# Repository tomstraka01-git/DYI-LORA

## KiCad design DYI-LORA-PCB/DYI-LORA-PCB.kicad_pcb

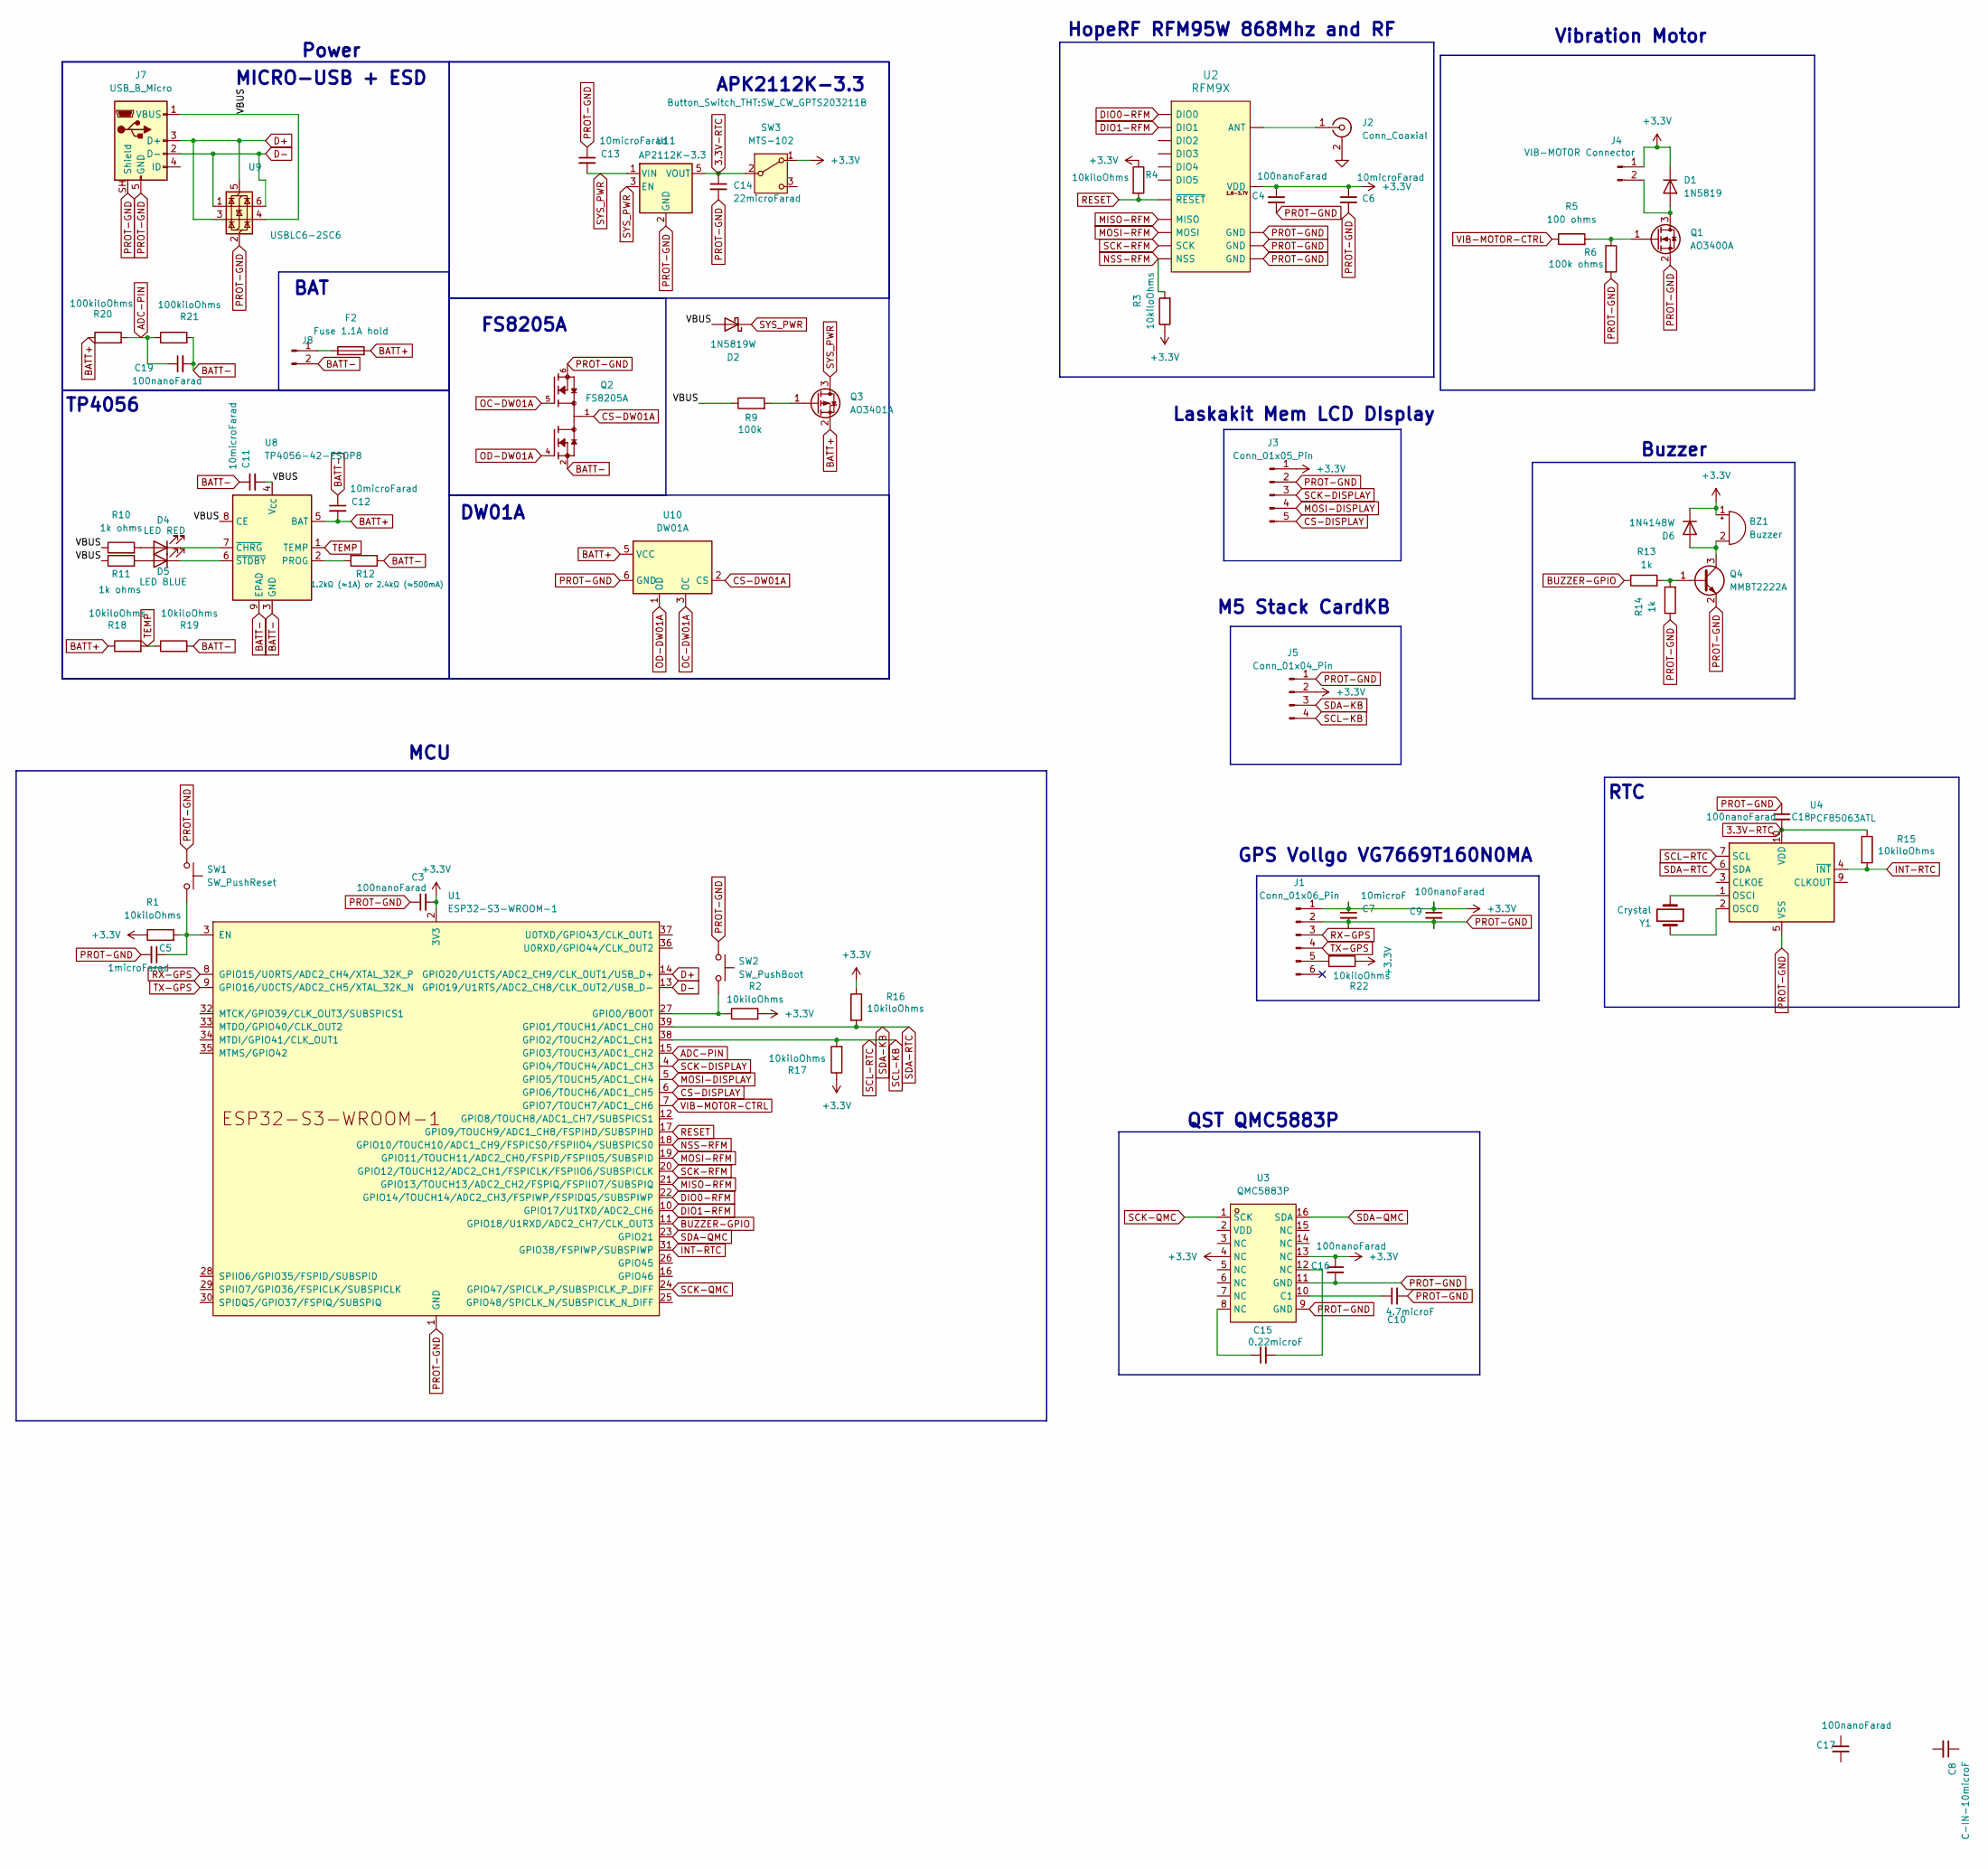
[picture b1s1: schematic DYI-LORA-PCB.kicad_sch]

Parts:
BZ1: Buzzer; MagneticBuzzer_PUI_AT-0927-TT-6-R
C3, C4, C9, C16, C17, C18, C19: 100nanoFarad; C_0603_1608Metric_Pad1.08x0.95mm_HandSolder
C5: 1microFarad; C_1206_3216Metric_Pad1.33x1.80mm_HandSolder
C6, C11, C12, C13: 10microFarad; C_0805_2012Metric_Pad1.18x1.45mm_HandSolder
C7: 10microF; C_0805_2012Metric_Pad1.18x1.45mm_HandSolder
C8: C-IN-10microF; C_0805_2012Metric_Pad1.18x1.45mm_HandSolder
C10: 4.7microF; C_0805_2012Metric_Pad1.18x1.45mm_HandSolder
C14: 22microFarad; C_1206_3216Metric_Pad1.33x1.80mm_HandSolder
C15: 0.22microF; C_0805_2012Metri
D1: 1N5819; D_SOD-123
D2: 1N5819W; D_SOD-123
D4: LED RED; LED_0805_2012Metric_Pad1.15x1.40mm_HandSolder
D5: LED BLUE; LED_0805_2012Metric_Pad1.15x1.40mm_HandSolder
D6: 1N4148W; D_SOD-123
F2: Fuse 1.1A hold; Fuse_1206_3216Metric_Pad1.42x1.75mm_HandSolder
J1: Conn_01x06_Pin; JST_SH_SM06B-SRSS-TB_1x06-1MP_P1.00mm_Horizontal
J2: Conn_Coaxial; SMA_Amphenol_132134-11_Vertical
J3: Conn_01x05_Pin; PinHeader_1x05_P2.54mm_Vertical
J4: VIB-MOTOR Connector; PinHeader_1x02_P2.54mm_Vertical
J5: Conn_01x04_Pin; JST_SH_SM04B-SRSS-TB_1x04-1MP_P1.00mm_Horizontal
J7: USB_B_Micro; USB_Micro-B_Molex_47346-0001
J8: Conn_01x02_Pin; JST_PH_S2B-PH-K_1x02_P2.00mm_Horizontal
Q1: AO3400A; SOT-23_Handsoldering
Q2: FS8205A; TSSOP-8_4.4x3mm_P0.65mm; PARTREV 1.7
Q3: AO3401A; SOT-23_Handsoldering
Q4: MMBT2222A; SOT-23_Handsoldering
R1, R2, R3, R4, R15, R16, R17, R18, R19, R22: 10kiloOhms; R_1206_3216Metric_Pad1.30x1.75mm_HandSolder
R5: 100 ohms; R_1206_3216Metric_Pad1.30x1.75mm_HandSolder
R6: 100k ohms; R_1206_3216Metric_Pad1.30x1.75mm_HandSolder
R9: 100k; R_0805_2012Metric_Pad1.20x1.40mm_HandSolder
R10, R11: 1k ohms; R_1206_3216Metric_Pad1.30x1.75mm_HandSolder
R12: 1.2kΩ (≈1A) or 2.4kΩ (≈500mA); R_1206_3216Metric_Pad1.30x1.75mm_HandSolder
R13, R14: 1k; R_0805_2012Metric_Pad1.20x1.40mm_HandSolder
R20, R21: 100kiloOhms; R_1206_3216Metric_Pad1.30x1.75mm_HandSolder
SW1: SW_PushReset; SW_PUSH_6mm_H4.3mm
SW2: SW_PushBoot; SW_PUSH_6mm_H4.3mm
SW3: MTS-102; SW_CW_GPTS203211B
U1: ESP32-S3-WROOM-1
U2: RFM9X; RFM9X-SMD
U3: QMC5883P; LGA-16_3x3mm_P0.5mm; MPN QMC5883P; LCSC Part C2847467
U4: PCF85063ATL; DFN-10-1EP_2.6x2.6mm_P0.5mm_EP1.3x2.2mm
U8: TP4056-42-ESOP8; SOIC-8-1EP_3.9x4.9mm_P1.27mm_EP2.41x3.3mm_ThermalVias
U9: USBLC6-2SC6; SOT-23-6
U10: DW01A; SOT-23-6
U11: AP2112K-3.3; SOT-23-5_HandSoldering
Y1: Crystal; Crystal_SMD_3215-2Pin_3.2x1.5mm

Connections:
3.3V-RTC: C14.1, C18.2, R15.1, SW3.2 (B), U4.10 (VDD), U11.5 (VOUT)
+3.3V: BZ1.1 (+), C3.2, C4.1, C6.1, C7.1, C9.1, C16.1, D1.1 (K), D6.1 (K), J1.1, J3.1, J4.1, J5.2, R1.1, R2.2, R3.1, R4.1, R16.1, R17.1, R22.1, SW3.1 (A), U1.2 (3V3), U2.13 (VDD), U3.4 (NC), U3.13 (NC)
/VBUS: C11.2, D2.2 (A), J7.1 (VBUS), R9.1, R10.1, R11.1, U8.4 (V_{CC}), U8.8 (CE), U9.4 (I/O2)
ADC-PIN: C19.1, R20.2, R21.1, U1.15 (GPIO3/TOUCH3/ADC1_CH2)
BATT+: C12.2, F2.2, Q3.2 (S), R18.1, R20.1, U8.5 (BAT), U10.5 (VCC)
BATT-: C11.1, C12.1, C19.2, J8.2, Q2.2, Q2.3, R12.1, R19.2, R21.2, U8.3 (GND), U8.9 (EPAD)
BUZZER-GPIO: R13.1, U1.11 (GPIO18/U1RXD/ADC2_CH7/CLK_OUT3)
CS-DISPLAY: J3.5, U1.6 (GPIO6/TOUCH6/ADC1_CH5)
CS-DW01A: Q2.1, Q2.8, U10.2 (CS)
D+: J7.3 (D+), U1.14 (GPIO20/U1CTS/ADC2_CH9/CLK_OUT1/USB_D+), U9.3 (I/O2), U9.5 (VBUS)
D-: J7.2 (D-), U1.13 (GPIO19/U1RTS/ADC2_CH8/CLK_OUT2/USB_D-), U9.1 (I/O1), U9.6 (I/O1)
DIO0-RFM: U1.22 (GPIO14/TOUCH14/ADC2_CH3/FSPIWP/FSPIDQS/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), U2.14 (DIO0)
DIO1-RFM: U1.10 (GPIO17/U1TXD/ADC2_CH6), U2.15 (DIO1)
GND: J2.2 (Ext)
INT-RTC: R15.2, U1.31 (GPIO38/FSPIWP/SUBSPIWP), U4.4 (~INT)
MISO-RFM: U1.21 (GPIO13/TOUCH13/ADC2_CH2/FSPIQ/FSPIIO7/S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), U2.2 (MISO)
MOSI-DISPLAY: J3.4, U1.5 (GPIO5/TOUCH5/ADC1_CH4)
MOSI-RFM: U1.19 (GPIO11/TOUCH11/ADC2_CH0/FSPID/FSPIIO5/S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), U2.3 (MOSI)
NSS-RFM: R3.2, U1.18 (GPIO10/TOUCH10/ADC1_CH9/FSPICS0/FSPIIO4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), U2.5 (NSS)
unnamed: BZ1.2 (-), D6.2 (A), Q4.3 (C)
unnamed: C15.1, U3.8 (NC)
unnamed: C15.2, U3.12 (NC)
unnamed: D1.2 (A), J4.2, Q1.3 (D)
unnamed: D4.2 (A), R10.2
unnamed: D4.1 (K), U8.7 (~CHRG)
unnamed: D5.2 (A), R11.2
unnamed: D5.1 (K), U8.6 (~STDBY)
unnamed: J1.5, R22.2
unnamed: J2.1 (In), U2.9 (ANT)
unnamed: F2.1, J8.1
unnamed: Q1.1 (G), R5.2, R6.1
unnamed: Q3.1 (G), R9.2
unnamed: Q4.1 (B), R13.2, R14.2
unnamed: C5.1, R1.2, SW1.2, U1.3 (EN)
unnamed: R2.1, SW2.2, U1.27 (GPIO0/BOOT)
unnamed: C10.1, U3.10 (C1)
unnamed: U4.1 (OSCI), Y1.1
unnamed: U4.2 (OSCO), Y1.2
unnamed: R12.2, U8.2 (PROG)
OC-DW01A: Q2.5, U10.3 (OC)
OD-DW01A: Q2.4, U10.1 (OD)
PROT-GND: C3.1, C4.2, C5.2, C6.2, C7.2, C9.2, C10.2, C13.1, C14.2, C16.2, C18.1, J1.2, J3.2, J5.1, J7.5 (GND), J7.SH (Shield), Q1.2 (S), Q2.6, Q2.7, Q4.2 (E), R6.2, R14.1, SW1.1, SW2.1, U1.1 (GND), U1.40 (GND), U1.41 (GND), U2.1 (GND), U2.8 (GND), U2.10 (GND), U3.9 (GND), U3.11 (GND), U4.5 (VSS), U9.2 (GND), U10.6 (GND), U11.2 (GND)
RESET: R4.2, U1.17 (GPIO9/TOUCH9/ADC1_CH8/FSPIHD/SUBSPIHD), U2.6 (~RESET)
RX-GPS: J1.3, U1.8 (GPIO15/U0RTS/ADC2_CH4/XTAL_32K_P)
SCK-DISPLAY: J3.3, U1.4 (GPIO4/TOUCH4/ADC1_CH3)
SCK-QMC: U1.24 (GPIO47/SPICLK_P/SUBSPICLK_P_DIFF), U3.1 (SCK)
SCK-RFM: U1.20 (GPIO12/TOUCH12/ADC2_CH1/FSPICLK/FSPIIO6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), U2.4 (SCK)
SCL-KB: J5.4, R17.2, U1.38 (GPIO2/TOUCH2/ADC1_CH1), U4.7 (SCL)
SDA-KB: J5.3, R16.2, U1.39 (GPIO1/TOUCH1/ADC1_CH0), U4.6 (SDA)
SDA-QMC: U1.23 (GPIO21), U3.16 (SDA)
SYS_PWR: C13.2, D2.1 (K), Q3.3 (D), U11.1 (VIN), U11.3 (EN)
TEMP: R18.2, R19.1, U8.1 (TEMP)
TX-GPS: J1.4, U1.9 (GPIO16/U0CTS/ADC2_CH5/XTAL_32K_N)
VIB-MOTOR-CTRL: R5.1, U1.7 (GPIO7/TOUCH7/ADC1_CH6)

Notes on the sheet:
RTC
TP4056
Vibration Motor
MCU
Buzzer
Power
GPS Vollgo VG7669T160N0MA
MICRO-USB + ESD
Laskakit Mem LCD DIsplay
APK2112K-3.3
HopeRF RFM95W 868Mhz and RF
QST QMC5883P
DW01A
M5 Stack CardKB
FS8205A
BAT

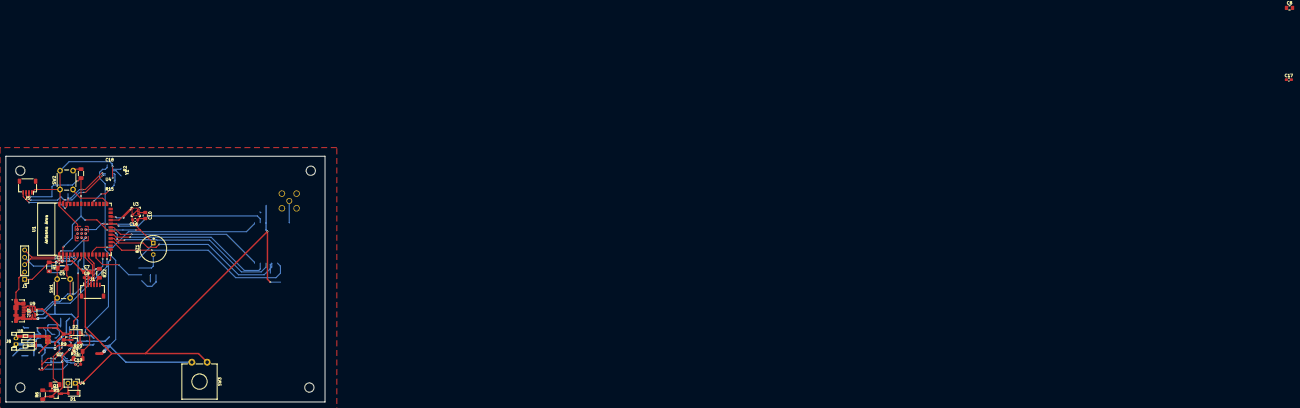
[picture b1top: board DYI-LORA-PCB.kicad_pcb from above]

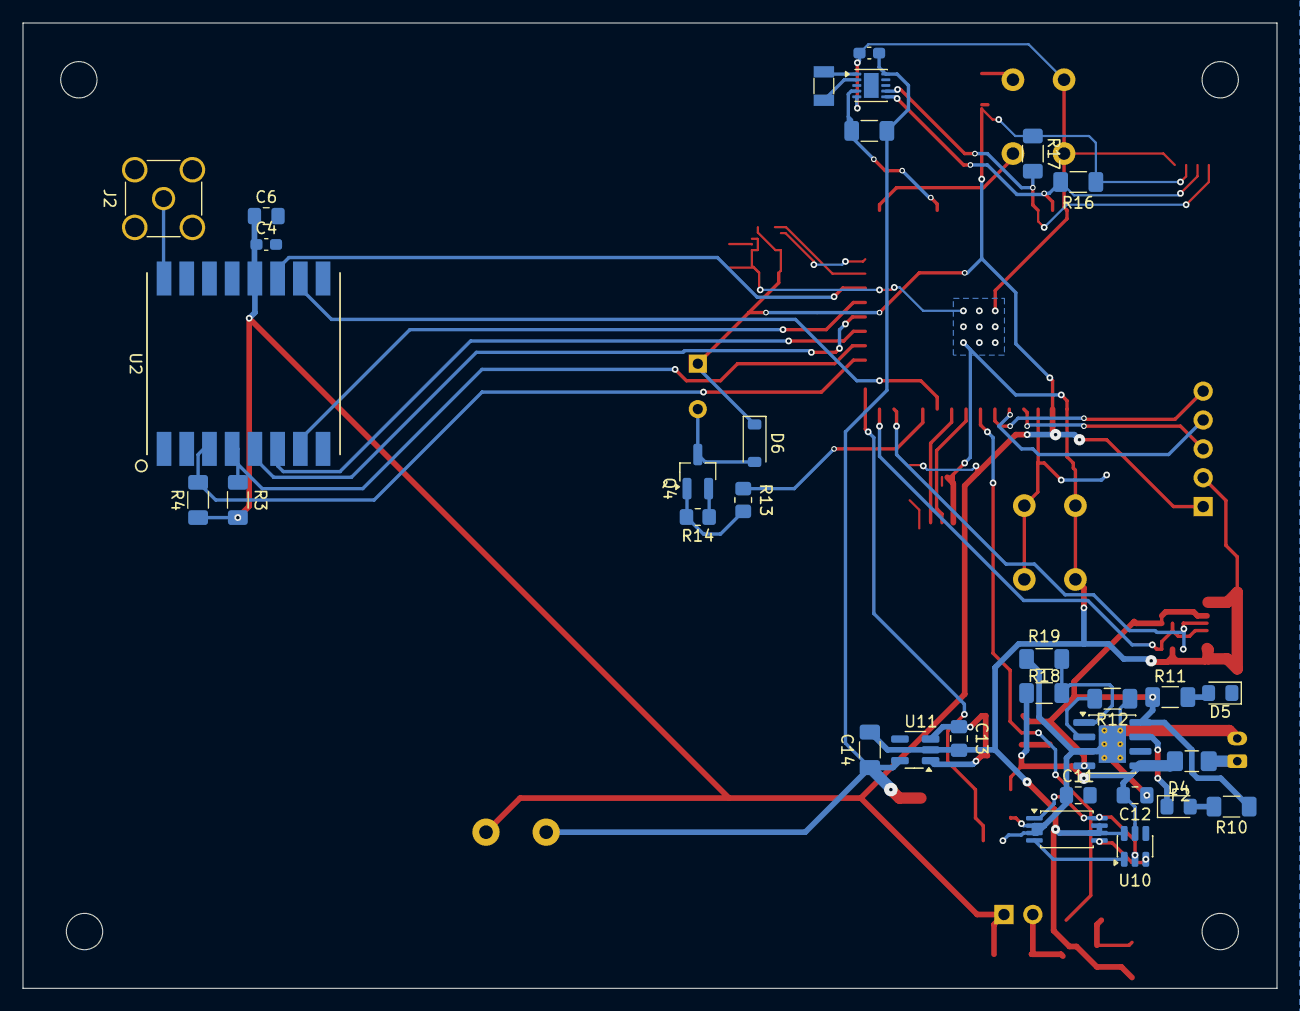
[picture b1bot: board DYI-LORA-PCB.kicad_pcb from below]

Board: 2 copper layers, 110.4 x 85.0 mm, 66 parts (32 on the bottom side), 51 nets.
